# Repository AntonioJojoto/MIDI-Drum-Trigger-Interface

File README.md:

# Low-Cost MIDI Drum Trigger Interface

Many people may not know this, but drums are expensive, and if you live in an apartment, you can't just buy a cheap acoustic set and play, as your neighbors will call the police before you can finish playing your first song because an acoustic set can easily reach +110 dB.

However, there is another option, electronic drums. They are so silent that your roommates won't even complain (if you play at 3AM they might). But there is one **big** drawback to edrums, they are **too expensive**.

A low-tier edrum can go around 400€, I currently own a Yamaha DTX450k and I got a deal for it at 440€, as it normally goes for 550€ and when I was staring to practice it was OK, but then I got the chance to practice for a year on a acoustic set, and when I had to return to my cheap set I started to notice the drawback of cheap electronic drumsets. 

Here are some problems that you may encounter when you play a cheap electronic set:
- The sounds from the module are awful, specially the cymbals.
- The pads are tiny and hard, in my Yamaha Drumset, they are 8 inches wide.
- All the pads and cymbals are single-zone, so no rimshot, bell sound or anything else.
- Hihat pedal is only in open or closed position, you can't get a lot of sounds from it.
- In my case, as I like to play hard, the drum rack was moving a lot. The snare is always falling.

Sure, all of these problems may disappear as you upgrade to a more expensive drum set, but you will have to spend around 1200€. But even then, it will still be a mid-tier electronic drumset.

The best option, in my opinion, is to convert an acoustic set into an electronic one. If you already have an acoustic set or if you don't have one, as you can get one for 100€ or 200€. Now, there are two options for electronic conversion, buy the triggers and cymbals or go the DIY route, which is **much cheaper**. Although there is one expensive component that all the DIY guides asks for, the **Drum Module**.

It is normally the most expensive component in every drumset. The job of this component is critical, read the signals from the triggers and make a sound accordingly. Drum modules can go for around 300€ to 700€, but instead of buying a module that produce a mediocre sound, you should buy or make a trigger interface, is the same a drum module but instead of producing the sounds by itself, it sends MIDI notes to your computer, which will always produce better sound than even the most expensive modules.

Trigger Interfaces are much cheaper, the DDrum Trigger Interface will work perfectly for only 170€, but you can even make this component yourself.

**DISCLAIMER**: From now on, the guide will center on build the interface, in the following months a guide on DIY trigger and cymbals will be available. But from now, there is plenty of information online.

# Current Features
- 16 single-zone channels.
- Custom values for each channel (scan time,dead time,etc).
- MIDI-over-USB Interface.
- Less than 3 milliseconds latency.

# Future Features
- [x] Schematic. 
- [x] Cross-Talk.
- [ ] Support for custom dual and triple zone cymbals.
- [ ] Support for rimshot on snare. 
- [ ] Hihat Pedal using optical sensor.
- [ ] Change values using LCD screen and keypad.
- [ ] Save custom values in EEPROM.
- [ ] PCB available for production.

# How it works?

There are many Arduino drum modules online, but a common problem in all of them is the latency, I find that an Arduino isn't fast enough to process the raw piezo signal from several channels, which is the approach that many people follow when making the interface. 

As seen in the picture, the peak of a piezo may only occur in the span of 100us. So the microcontroller may not read the channel at just the peak, so it will send no MIDI value at all, or send a wrong value. That is why in my desing I decided to add a **peak detector circuit** per channel.

This circuit maintains the highest voltage from the piezo, so the voltage of the peak will be available for the uC to be read. Once the peak value has been registered, the capacitor will be discharged through the transistor, reseting the peak detector.

- **Yellow Signal**: Raw piezo signal.
- **Blue Signal**: Peak detector output.
- **Pink Signal**: Transistor gate.

Once the uC detects a value on the channels higher than a given **threshold**, it wait a couple of milliseconds for the signal to reach the peak, this period is called **scan time**, after that, the value of the channel is read. But to stop retriggering, the uC won't clear the detector once a **dead time** has finished. All of these values are standarts from drum modules, and they can be set from channel to channel. 

Using this method, we ensure that only the peak value of the piezo will be read, also no hits will be lost because the uC can read each channel at its own pace. In this example, the hit was a flam, and it registered both hits, although they were 30 milliseconds apart.

# List of materials.

This desing is centered arround the AtMega 2560, as I want more than 6 channels for a full electronic set. But an AtMega328p can also be used, it depends on the number of channels that you want to use.

### Material per module.
- AtMega 2560 or AtMega328p. Although I recommend an Arduino, as the AtMega16 will be used to send the MIDI events over USB.
- ISP Programmer: USBTiny or another Arduino.
- LM7660 positive to negative voltage converter. 

### Materials per channel.

- Female Jack (3.5mm or 6.5mm).
- Male Jack (3.5mm or 6.5mm).
- 2N2222 NPN BJT.
- 10k and 330 resistors.
- 1uF ceramic capacitor.
- 1N4148 Diode.
- TL082 Operational Amplifier.

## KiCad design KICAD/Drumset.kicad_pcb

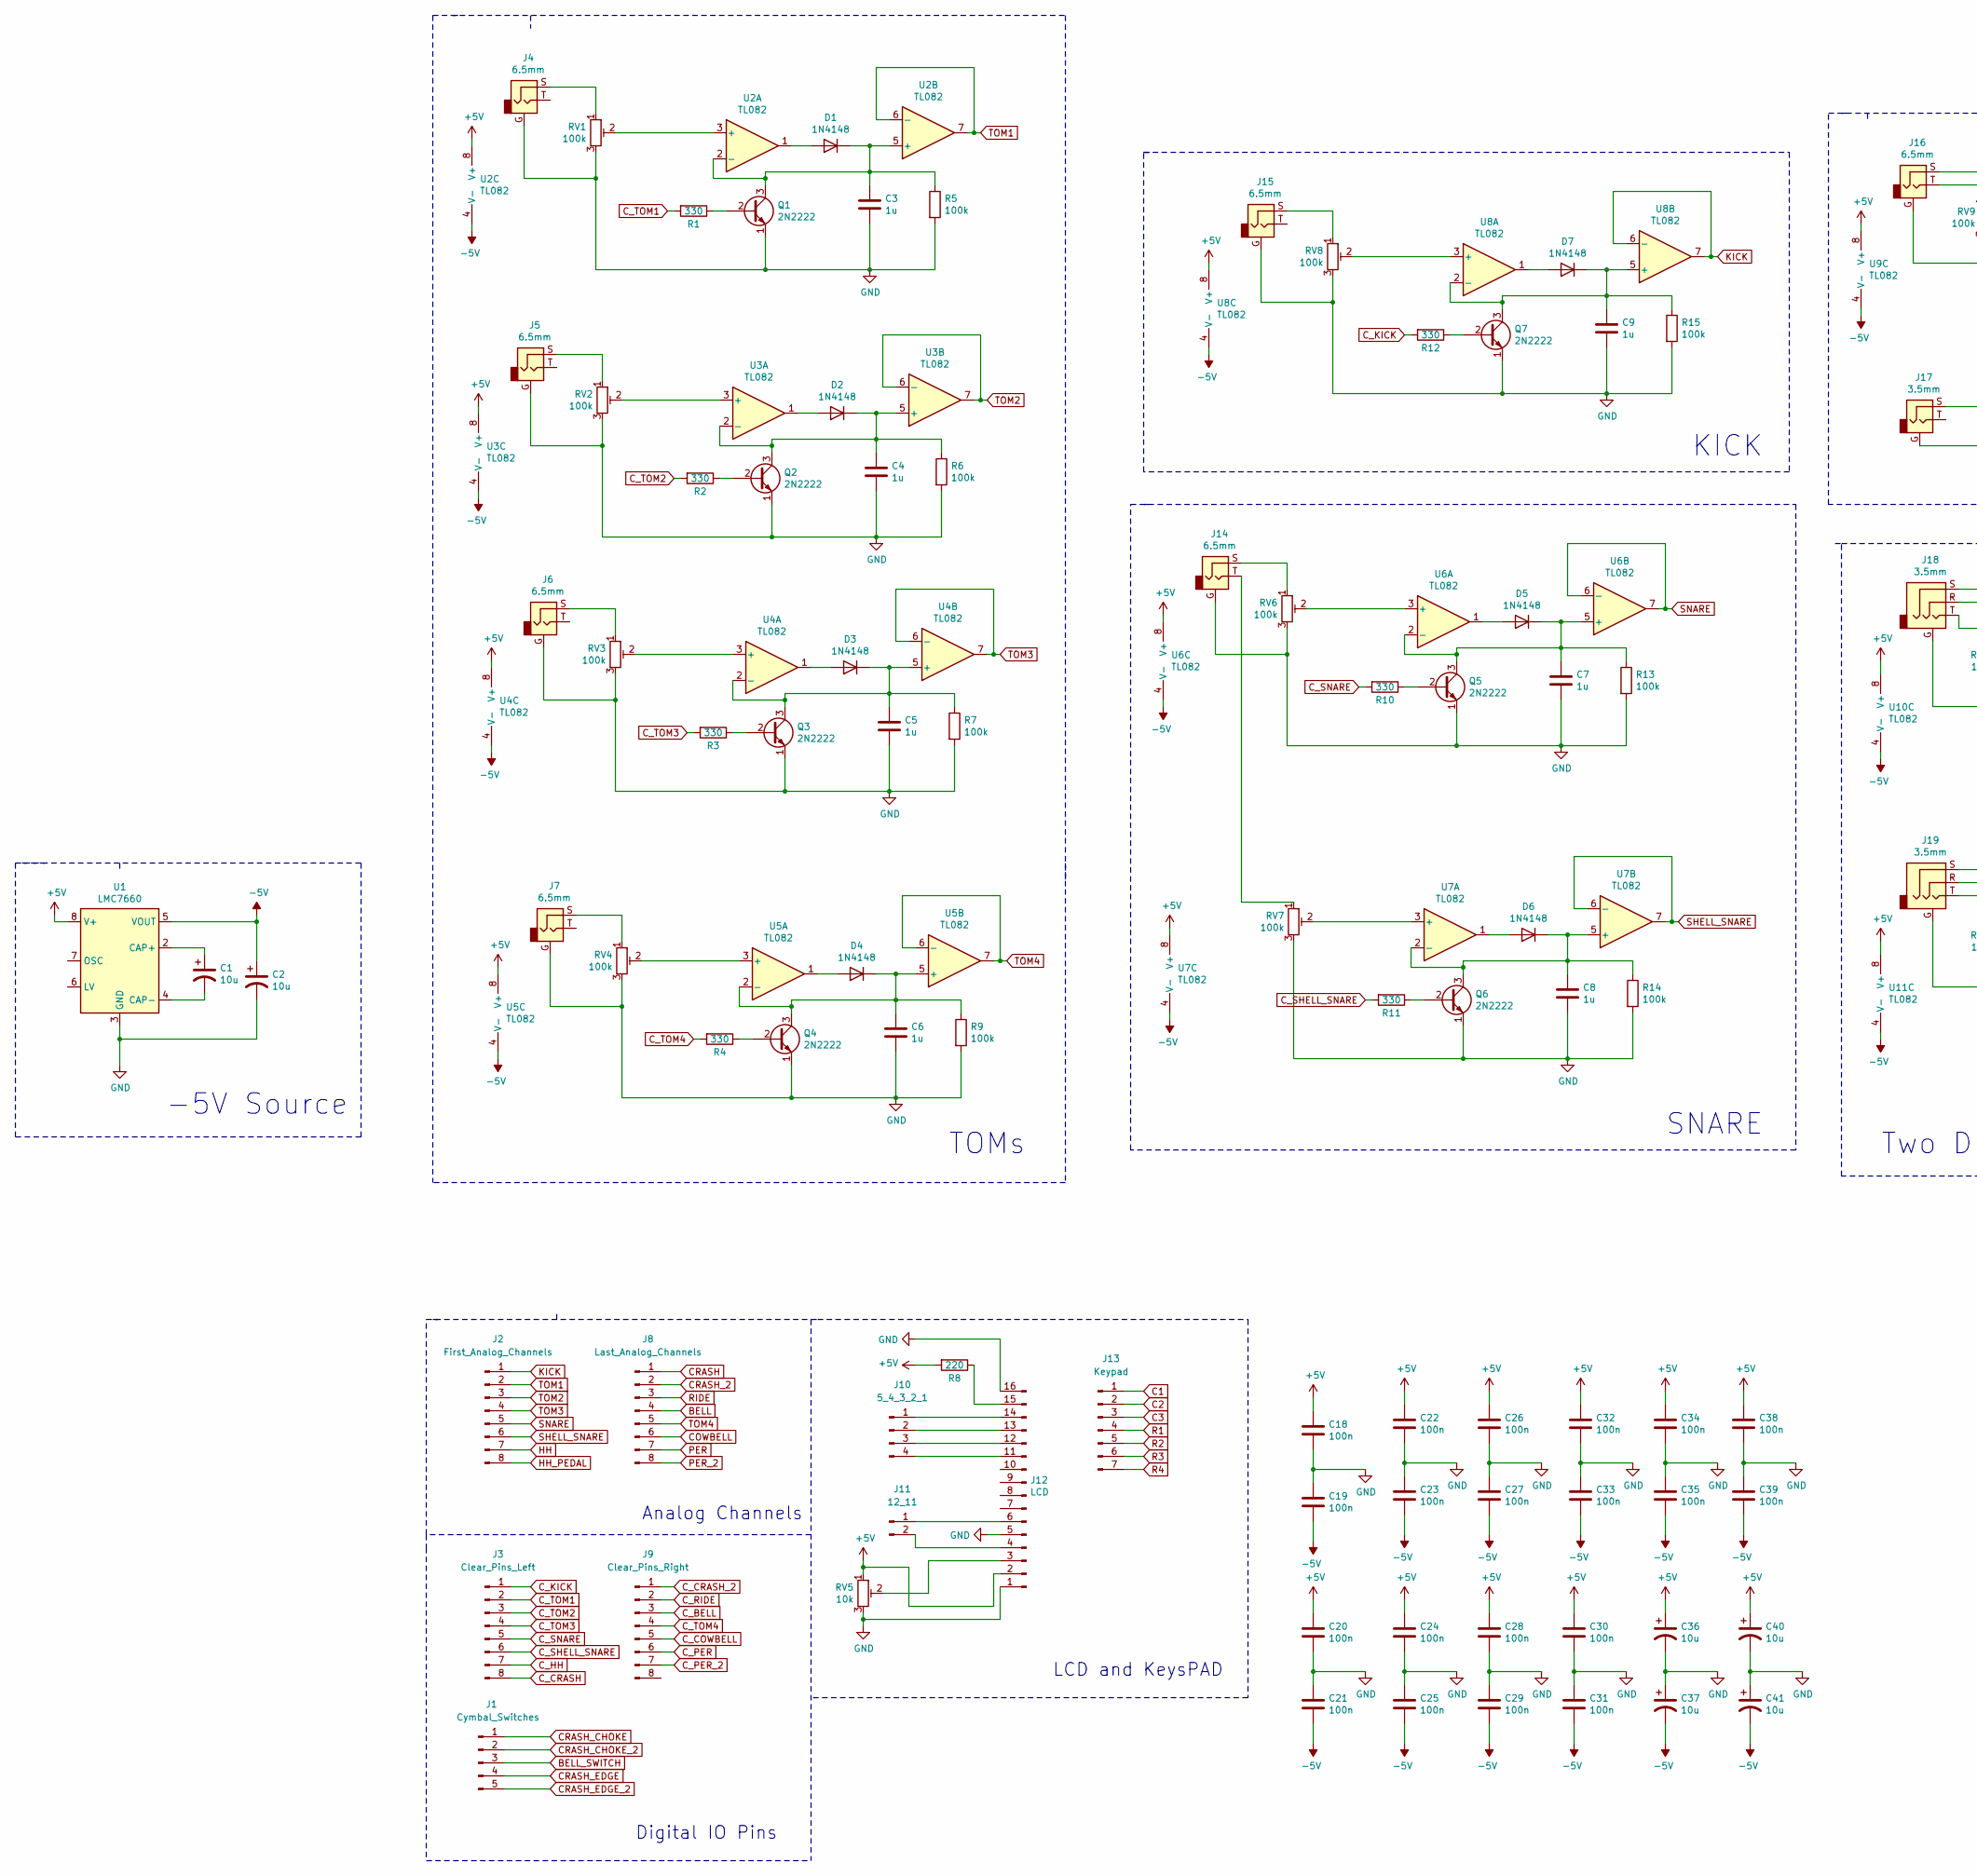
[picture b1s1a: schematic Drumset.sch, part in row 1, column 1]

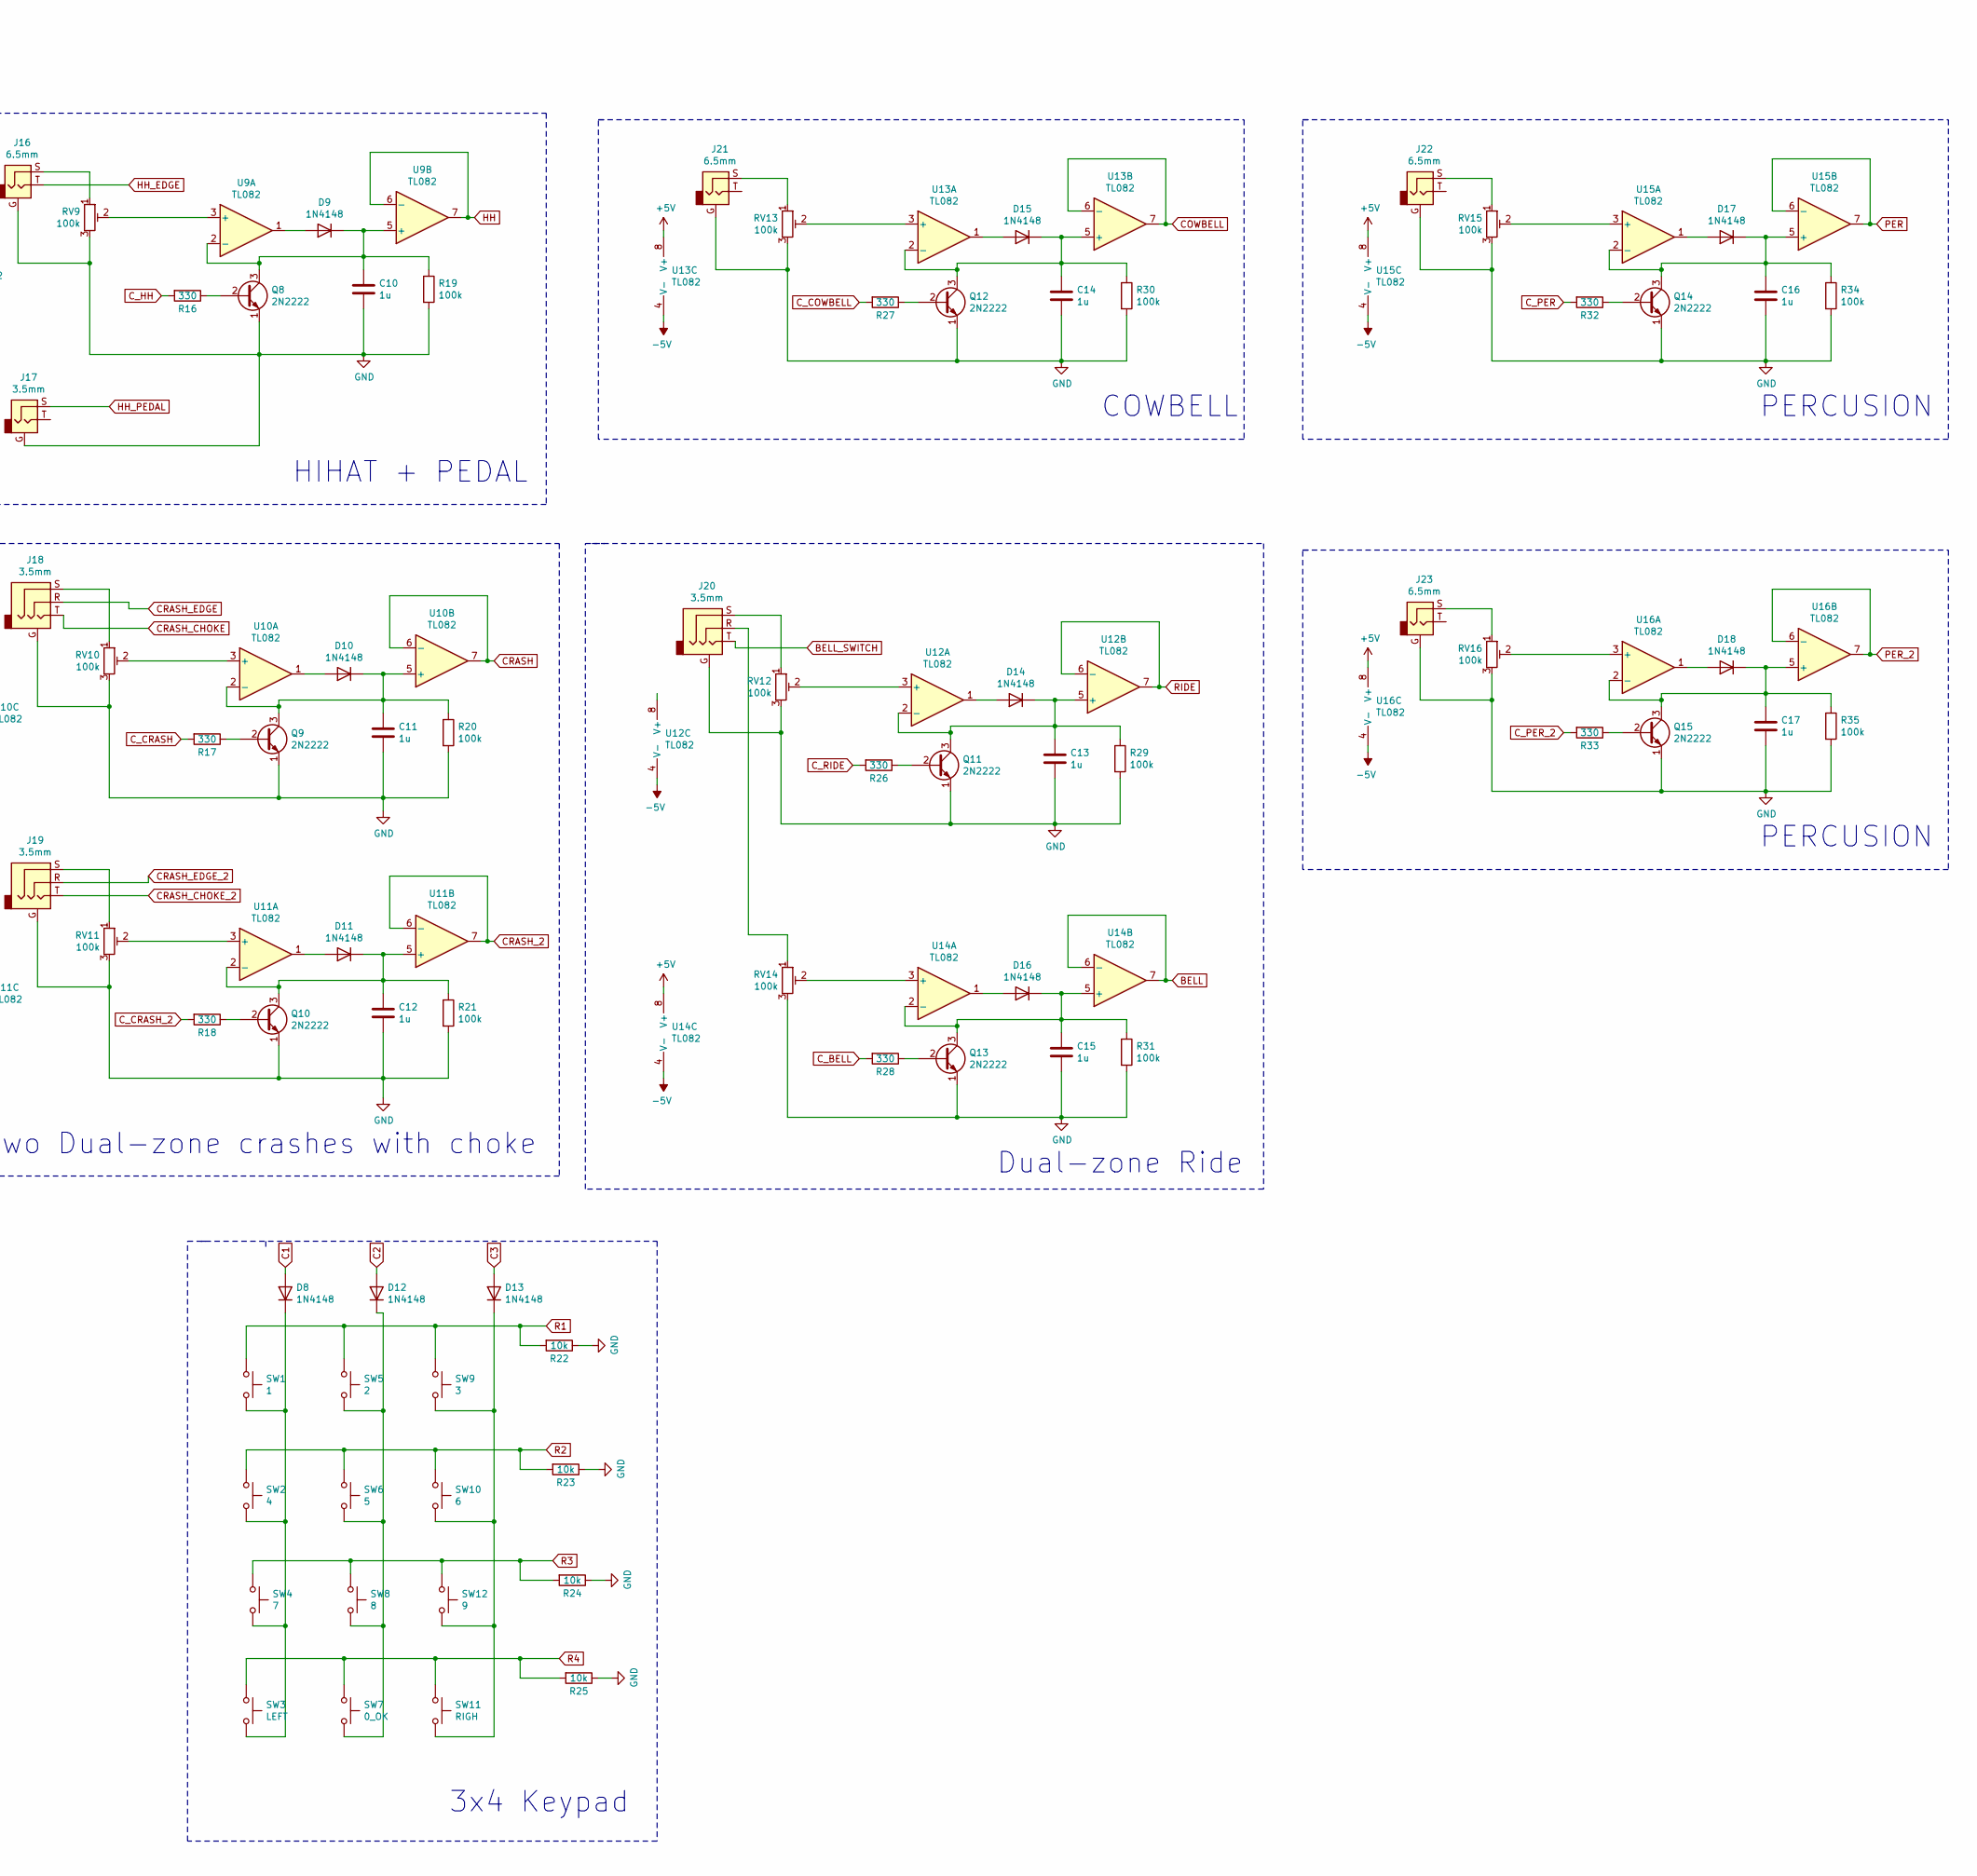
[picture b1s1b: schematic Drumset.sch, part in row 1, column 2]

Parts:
C1, C2, C40, C41: 10u; CP_Radial_D6.3mm_P2.50mm
C3, C4, C5, C6, C7, C8, C9, C10, C11, C12, C13, C14, C15, C16, C17: 1u; C_Disc_D8.0mm_W5.0mm_P5.00mm
C18, C19, C20, C21, C22, C23, C24, C25, C26, C27, C28, C29, C30, C31, C32, C33, C34, C35, C38, C39: 100n; C_Disc_D3.8mm_W2.6mm_P2.50mm
C36, C37: 10u; C_Disc_D3.8mm_W2.6mm_P2.50mm
D1, D2, D3, D4, D5, D6, D7, D8, D9, D10, D11, D12, D13, D14, D15, D16, D17, D18: 1N4148; D_DO-35_SOD27_P10.16mm_Horizontal
J1: Cymbal_Switches; PinHeader_1x05_P2.54mm_Vertical
J2: First_Analog_Channels; PinHeader_1x08_P2.54mm_Vertical
J3: Clear_Pins_Left; PinHeader_1x08_P2.54mm_Vertical
J4, J5, J6, J7, J14, J15, J16, J21, J22, J23: 6.5mm; Jack_6.35mm_Neutrik_NRJ6HM-1-AU_Horizontal
J8: Last_Analog_Channels; PinHeader_1x08_P2.54mm_Vertical
J9: Clear_Pins_Right; PinHeader_1x08_P2.54mm_Vertical
J10: 5_4_3_2_1; PinHeader_1x05_P2.54mm_Vertical
J11: 12_11; PinHeader_1x02_P2.54mm_Vertical
J12: LCD; PinHeader_1x16_P2.54mm_Vertical
J13: Keypad; PinHeader_1x07_P2.54mm_Vertical
J17, J18, J19, J20: 3.5mm; Jack_3.5mm_PJ320D_Horizontal
Q1, Q2, Q3, Q4, Q5, Q6, Q7, Q8, Q9, Q10, Q11, Q12, Q13, Q14, Q15: 2N2222; TO-92_Inline_Wide
R1, R2, R3, R4, R10, R11, R12, R16, R17, R18, R26, R27, R28, R32, R33: 330; R_Axial_DIN0207_L6.3mm_D2.5mm_P10.16mm_Horizontal
R5, R6, R7, R9, R13, R14, R15, R19, R20, R21, R29, R30, R31, R34, R35: 100k; R_Axial_DIN0207_L6.3mm_D2.5mm_P10.16mm_Horizontal
R8: 220; R_Axial_DIN0207_L6.3mm_D2.5mm_P10.16mm_Horizontal
R22, R23, R24, R25: 10k; R_Axial_DIN0207_L6.3mm_D2.5mm_P10.16mm_Horizontal
RV1, RV2, RV3, RV4, RV6, RV7, RV8, RV9, RV10, RV11, RV12, RV13, RV14, RV15, RV16: 100k; Potentiometer_Bourns_3266Y_Vertical
RV5: 10k; Potentiometer_Piher_PT-10-V05_Vertical
SW1: 1; SW_PUSH_6mm_H4.3mm
SW2: 4; SW_PUSH_6mm_H4.3mm
SW3: LEFT; SW_PUSH_6mm_H4.3mm
SW4: 7; SW_PUSH_6mm_H4.3mm
SW5: 2; SW_PUSH_6mm_H4.3mm
SW6: 5; SW_PUSH_6mm_H4.3mm
SW7: 0_OK; SW_PUSH_6mm_H4.3mm
SW8: 8; SW_PUSH_6mm_H4.3mm
SW9: 3; SW_PUSH_6mm_H4.3mm
SW10: 6; SW_PUSH_6mm_H4.3mm
SW11: RIGH; SW_PUSH_6mm_H4.3mm
SW12: 9; SW_PUSH_6mm_H4.3mm
U1: LMC7660; DIP-8_W7.62mm_Socket
U2, U3, U4, U5, U6, U7, U8, U9, U10, U11, U12, U13, U14, U15, U16: TL082; DIP-8_W7.62mm_Socket

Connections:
+5V: C18.1, C20.1, C22.1, C24.1, C26.1, C28.1, C30.1, C32.1, C34.1, C36.1, C38.1, C40.1, J12.2, R8.2, RV5.1, U1.8 (V+), U2.8 (V+), U3.8 (V+), U4.8 (V+), U5.8 (V+), U6.8 (V+), U7.8 (V+), U8.8 (V+), U9.8 (V+), U10.8 (V+), U11.8 (V+), U13.8 (V+), U14.8 (V+), U15.8 (V+), U16.8 (V+)
-5V: C2.1, C19.2, C21.2, C23.2, C25.2, C27.2, C29.2, C31.2, C33.2, C35.2, C37.2, C39.2, C41.2, U1.5 (VOUT), U2.4 (V-), U3.4 (V-), U4.4 (V-), U5.4 (V-), U6.4 (V-), U7.4 (V-), U8.4 (V-), U9.4 (V-), U10.4 (V-), U11.4 (V-), U12.4 (V-), U13.4 (V-), U14.4 (V-), U15.4 (V-), U16.4 (V-)
BELL: J8.4, U14.6 (-), U14.7
BELL_SWITCH: J1.3, J20.T
C1: D8.2 (A), J13.1
C2: D12.2 (A), J13.2
C3: D13.2 (A), J13.3
COWBELL: J8.6, U13.6 (-), U13.7
CRASH: J8.1, U10.6 (-), U10.7
CRASH_2: J8.2, U11.6 (-), U11.7
CRASH_CHOKE: J1.1, J18.T
CRASH_CHOKE_2: J1.2, J19.T
CRASH_EDGE: J1.4, J18.R
CRASH_EDGE_2: J1.5, J19.R
C_BELL: J9.3, R28.2
C_COWBELL: J9.5, R27.2
C_CRASH: J3.8, R17.2
C_CRASH_2: J9.1, R18.2
C_HH: J3.7, R16.2
C_KICK: J3.1, R12.2
C_PER: J9.6, R32.2
C_PER_2: J9.7, R33.2
C_RIDE: J9.2, R26.2
C_SHELL_SNARE: J3.6, R11.2
C_SNARE: J3.5, R10.2
C_TOM1: J3.2, R1.2
C_TOM2: J3.3, R2.2
C_TOM3: J3.4, R3.2
C_TOM4: J9.4, R4.2
GND: C2.2, C3.2, C4.2, C5.2, C6.2, C7.2, C8.2, C9.2, C10.2, C11.2, C12.2, C13.2, C14.2, C15.2, C16.2, C17.2, C18.2, C19.1, C20.2, C21.1, C22.2, C23.1, C24.2, C25.1, C26.2, C27.1, C28.2, C29.1, C30.2, C31.1, C32.2, C33.1, C34.2, C35.1, C36.2, C37.1, C38.2, C39.1, C40.2, C41.1, J4.G, J5.G, J6.G, J7.G, J12.1, J12.5, J12.16, J14.G, J15.G, J16.G, J17.G, J18.G, J19.G, J20.G, J21.G, J22.G, J23.G, Q1.1 (E), Q2.1 (E), Q3.1 (E), Q4.1 (E), Q5.1 (E), Q6.1 (E), Q7.1 (E), Q8.1 (E), Q9.1 (E), Q10.1 (E), Q11.1 (E), Q12.1 (E), Q13.1 (E), Q14.1 (E), Q15.1 (E), R5.2, R6.2, R7.2, R9.2, R13.2, R14.2, R15.2, R19.2, R20.2, R21.2, R22.1, R23.1, R24.1, R25.1, R29.2, R30.2, R31.2, R34.2, R35.2, RV1.3, RV2.3, RV3.3, RV4.3, RV5.3, RV6.3, RV7.3, RV8.3, RV9.3, RV10.3, RV11.3, RV12.3, RV13.3, RV14.3, RV15.3, RV16.3, U1.3 (GND)
HH: J2.7, U9.6 (-), U9.7
HH_EDGE: J16.T
HH_PEDAL: J2.8, J17.S
KICK: J2.1, U8.6 (-), U8.7
unnamed: C1.1, U1.2 (CAP+)
unnamed: C1.2, U1.4 (CAP-)
unnamed: C3.1, D1.1 (K), Q1.3 (C), R5.1, U2.2 (-), U2.5 (+)
unnamed: C4.1, D2.1 (K), Q2.3 (C), R6.1, U3.2 (-), U3.5 (+)
unnamed: C5.1, D3.1 (K), Q3.3 (C), R7.1, U4.2 (-), U4.5 (+)
unnamed: C6.1, D4.1 (K), Q4.3 (C), R9.1, U5.2 (-), U5.5 (+)
unnamed: C7.1, D5.1 (K), Q5.3 (C), R13.1, U6.2 (-), U6.5 (+)
unnamed: C8.1, D6.1 (K), Q6.3 (C), R14.1, U7.2 (-), U7.5 (+)
unnamed: C9.1, D7.1 (K), Q7.3 (C), R15.1, U8.2 (-), U8.5 (+)
unnamed: C10.1, D9.1 (K), Q8.3 (C), R19.1, U9.2 (-), U9.5 (+)
unnamed: C11.1, D10.1 (K), Q9.3 (C), R20.1, U10.2 (-), U10.5 (+)
unnamed: C12.1, D11.1 (K), Q10.3 (C), R21.1, U11.2 (-), U11.5 (+)
unnamed: C13.1, D14.1 (K), Q11.3 (C), R29.1, U12.2 (-), U12.5 (+)
unnamed: C14.1, D15.1 (K), Q12.3 (C), R30.1, U13.2 (-), U13.5 (+)
unnamed: C15.1, D16.1 (K), Q13.3 (C), R31.1, U14.2 (-), U14.5 (+)
unnamed: C16.1, D17.1 (K), Q14.3 (C), R34.1, U15.2 (-), U15.5 (+)
unnamed: C17.1, D18.1 (K), Q15.3 (C), R35.1, U16.2 (-), U16.5 (+)
unnamed: D1.2 (A), U2.1
unnamed: D2.2 (A), U3.1
unnamed: D3.2 (A), U4.1
unnamed: D4.2 (A), U5.1
unnamed: D5.2 (A), U6.1
unnamed: D6.2 (A), U7.1
unnamed: D7.2 (A), U8.1
unnamed: D8.1 (K), SW1.2, SW2.2, SW3.2, SW4.2
unnamed: D9.2 (A), U9.1
unnamed: D10.2 (A), U10.1
unnamed: D11.2 (A), U11.1
unnamed: D12.1 (K), SW5.2, SW6.2, SW7.2, SW8.2
unnamed: D13.1 (K), SW9.2, SW10.2, SW11.2, SW12.2
unnamed: D14.2 (A), U12.1
unnamed: D15.2 (A), U13.1
unnamed: D16.2 (A), U14.1
unnamed: D17.2 (A), U15.1
unnamed: D18.2 (A), U16.1
unnamed: J4.S, RV1.1
unnamed: J5.S, RV2.1
unnamed: J6.S, RV3.1
unnamed: J7.S, RV4.1
unnamed: J10.1, J12.14
unnamed: J10.2, J12.13
unnamed: J10.3, J12.12
unnamed: J10.4, J12.11
unnamed: J11.1, J12.6
unnamed: J11.2, J12.4
unnamed: J12.3, RV5.2
unnamed: J12.15, R8.1
unnamed: J14.S, RV6.1
unnamed: J14.T, RV7.1
unnamed: J15.S, RV8.1
unnamed: J16.S, RV9.1
unnamed: J18.S, RV10.1
unnamed: J19.S, RV11.1
unnamed: J20.R, RV14.1
unnamed: J20.S, RV12.1
unnamed: J21.S, RV13.1
unnamed: J22.S, RV15.1
unnamed: J23.S, RV16.1
unnamed: Q1.2 (B), R1.1
unnamed: Q2.2 (B), R2.1
unnamed: Q3.2 (B), R3.1
unnamed: Q4.2 (B), R4.1
unnamed: Q5.2 (B), R10.1
unnamed: Q6.2 (B), R11.1
unnamed: Q7.2 (B), R12.1
unnamed: Q8.2 (B), R16.1
unnamed: Q9.2 (B), R17.1
unnamed: Q10.2 (B), R18.1
unnamed: Q11.2 (B), R26.1
unnamed: Q12.2 (B), R27.1
unnamed: Q13.2 (B), R28.1
unnamed: Q14.2 (B), R32.1
unnamed: Q15.2 (B), R33.1
unnamed: RV1.2, U2.3 (+)
unnamed: RV2.2, U3.3 (+)
unnamed: RV3.2, U4.3 (+)
unnamed: RV4.2, U5.3 (+)
unnamed: RV6.2, U6.3 (+)
unnamed: RV7.2, U7.3 (+)
unnamed: RV8.2, U8.3 (+)
unnamed: RV9.2, U9.3 (+)
unnamed: RV10.2, U10.3 (+)
unnamed: RV11.2, U11.3 (+)
unnamed: RV12.2, U12.3 (+)
unnamed: RV13.2, U13.3 (+)
unnamed: RV14.2, U14.3 (+)
unnamed: RV15.2, U15.3 (+)
unnamed: RV16.2, U16.3 (+)
PER: J8.7, U15.6 (-), U15.7
PER_2: J8.8, U16.6 (-), U16.7
R1: J13.4, R22.2, SW1.1, SW5.1, SW9.1
R2: J13.5, R23.2, SW2.1, SW6.1, SW10.1
R3: J13.6, R24.2, SW4.1, SW8.1, SW12.1
R4: J13.7, R25.2, SW3.1, SW7.1, SW11.1
RIDE: J8.3, U12.6 (-), U12.7
SHELL_SNARE: J2.6, U7.6 (-), U7.7
SNARE: J2.5, U6.6 (-), U6.7
TOM1: J2.2, U2.6 (-), U2.7
TOM2: J2.3, U3.6 (-), U3.7
TOM3: J2.4, U4.6 (-), U4.7
TOM4: J8.5, U5.6 (-), U5.7

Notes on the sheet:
KICK
SNARE
-5V Source
HIHAT + PEDAL
Two Dual-zone crashes with choke
Dual-zone Ride
TOMs
COWBELL
PERCUSION
Analog Channels
3x4 Keypad
Digital IO Pins
LCD and KeysPAD

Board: 2 copper layers, 176 parts (0 on the bottom side), 134 nets, no tracks yet.

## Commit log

2020-09-12 Adding git ignore rules
2020-09-12 Making the README
2020-09-12 Adding pictures to the README
2020-09-12 Finishing README
2020-09-12 Aleki
2020-09-12 Finished README, errata for chech
2020-09-12 Adding the kicad files
2020-09-12 Fixed TODO list
2020-09-12 Comments in english, ready for branching
2020-09-12 Added a code for all the code
2020-09-12 Adding LCD feature
2020-09-12 Added button functions
2020-09-12 Fixed one function
2020-09-13 trying keypad with test, row ok, but not col.
2020-09-13 Fixed button.ino
2020-09-13 Testing
2020-09-14 Stable, 3 channels for prototype
2020-09-21 Stable with 3 channels DTX450k
2020-09-22 Fixed the 32 midi note error, check out 2 commits before
